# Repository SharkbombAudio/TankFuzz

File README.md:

# TankFuzz
Quad-stage silicone fuzz pedal.  Over-the-top with all the sustain you crave

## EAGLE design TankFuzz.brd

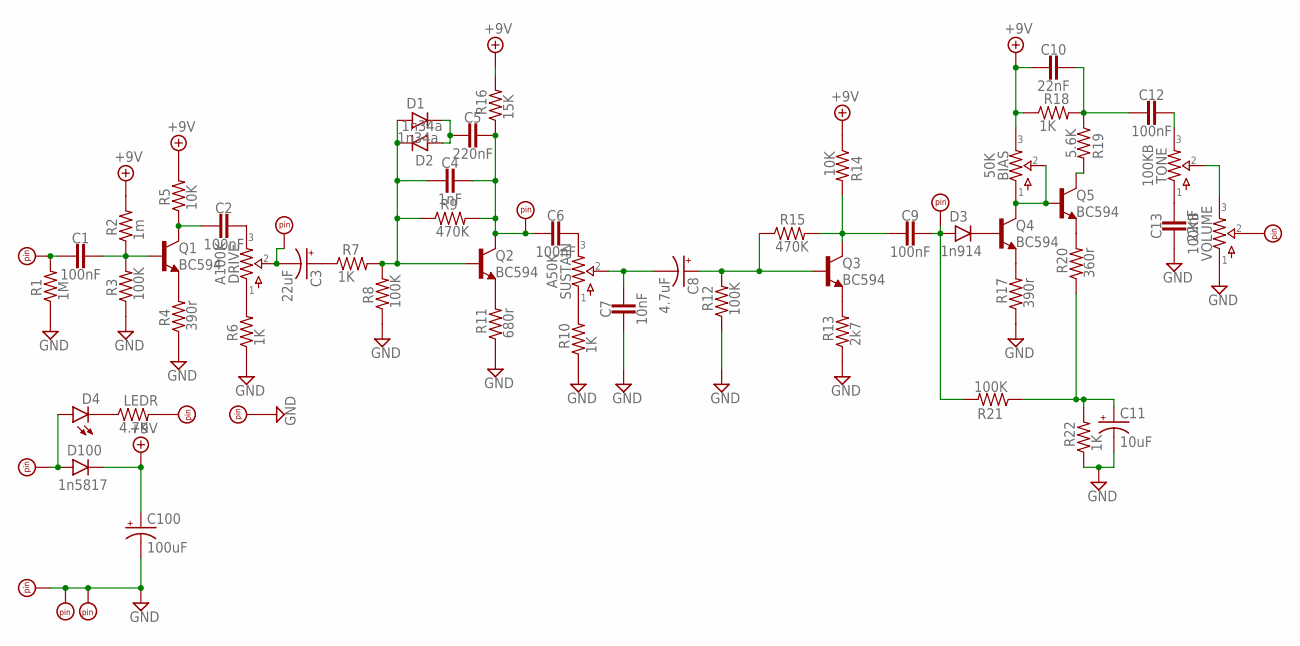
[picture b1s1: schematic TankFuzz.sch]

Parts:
BIAS: 50K; TRIM3
C1, C2, C6, C9, C12: 100nF; 0.2".MED
C3: 22uF; 050_020_1
C4: 1nF; 0.2".MED
C5: 220nF; 0.2".MED
C7: 10nF; 0.2".MED
C8: 4.7uF; 050_020_1
C10, C13: 22nF; 0.2".MED
C11: 10uF; 050_020_1
C100: 100uF; 050_020_1
D1, D2: 1n34a; DO35-3
D3: 1n914; DO35-3
D4: LED3MM
D100: 1n5817; DO41-3
DRIVE: A100K; 16MM_B.MOUNT
LEDR: 4.7K; R0207/3
Q1, Q2, Q3, Q4, Q5: BC594; TO92
R1: 1M; R0207/3
R2: 1m; R0207/3
R3, R8, R12, R21: 100K; R0207/3
R4, R17: 390r; R0207/3
R5, R14: 10K; R0207/3
R6, R7, R10, R18, R22: 1K; R0207/3
R9, R15: 470K; R0207/3
R11: 680r; R0207/3
R13: 2k7; R0207/3
R16: 15K; R0207/3
R19: 5.6K; R0207/3
R20: 360r; R0207/3
SUSTAIN: A50K; 16MM_B.MOUNT
TONE: 100KB; 16MM_B.MOUNT
U$1, U$2, U$3, U$4, U$5, U$6, U$8, U$9, U$10, U$11, U$12: PADS.RND_NL; PAD2
VOLUME: 100KB; 16MM_B.MOUNT

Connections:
+9V: BIAS.3, BIAS.6 (3), C10.2, C100.+, D100.C, R2.2, R5.2, R14.1, R16.2, R18.1
GND: C7.2, C11.-, C13.2, C100.-, R1.1, R3.1, R4.1, R6.1, R8.1, R10.1, R11.1, R12.1, R13.1, R17.1, R22.1, U$4.P$1, U$6.P$1, U$8.P$1, U$9.P$1, VOLUME.1
unnamed: C1.2, R1.2, U$1.P$1
unnamed: C1.1, Q1.2 (B), R2.1, R3.2
unnamed: Q1.3 (E), R4.2
unnamed: C2.2, Q1.1 (C), R5.1
unnamed: C2.1, DRIVE.3
unnamed: DRIVE.1, R6.2
unnamed: C3.-, DRIVE.2, U$10.P$1
unnamed: C3.+, R7.1
unnamed: C6.1, SUSTAIN.3
unnamed: Q2.3 (E), R11.2
unnamed: C4.1, C5.1, C6.2, Q2.1 (C), R9.2, R16.1, U$11.P$1
unnamed: C5.2, D1.C, D2.A
unnamed: C4.2, D1.A, D2.C, Q2.2 (B), R7.2, R8.2, R9.1
unnamed: R10.2, SUSTAIN.1
unnamed: C7.1, C8.-, SUSTAIN.2
unnamed: C8.+, Q3.2 (B), R12.2, R15.1
unnamed: Q3.3 (E), R13.2
unnamed: C9.2, Q3.1 (C), R14.2, R15.2
unnamed: C9.1, D3.A, R21.2, U$12.P$1
unnamed: D3.C, Q4.2 (B)
unnamed: Q4.3 (E), R17.2
unnamed: BIAS.1, BIAS.2, BIAS.4 (1), BIAS.5 (2), Q4.1 (C), Q5.2 (B)
unnamed: C12.1, TONE.3
unnamed: C10.1, C12.2, R18.2, R19.1
unnamed: Q5.1 (C), R19.2
unnamed: Q5.3 (E), R20.2
unnamed: C11.+, R20.1, R21.1, R22.2
unnamed: TONE.2, VOLUME.3
unnamed: C13.1, TONE.1
unnamed: U$2.P$1, VOLUME.2
unnamed: LEDR.2, U$5.P$1
unnamed: D4.A, D100.A, U$3.P$1
unnamed: D4.K (C), LEDR.1

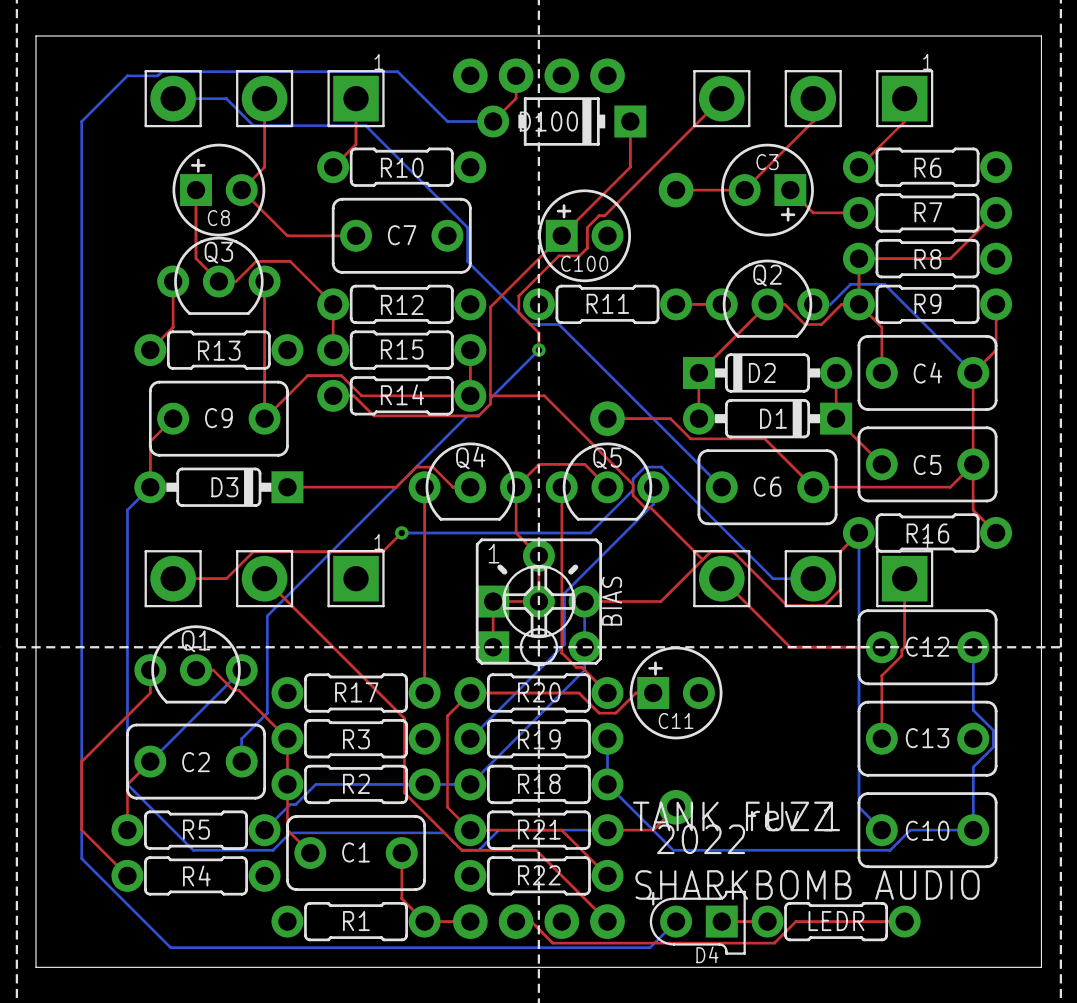
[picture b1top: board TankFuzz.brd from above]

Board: 2 copper layers, 55.9 x 51.7 mm, 64 parts (0 on the bottom side), 35 nets.

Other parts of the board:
U$7: 125B

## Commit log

2023-02-15 Initial commit of Tank Fuzz board+schematic
